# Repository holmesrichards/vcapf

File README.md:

# Voltage controlled all pass filter

***Note**: At this point the main PCB has been tested and found to be satisfactory, but the first run jacks PCB had errors. They have been corrected [twice] in the design and Gerber files but the [re]corrected board has not been tested. But what are the chances I'd get something so simple wrong ~~twice~~ three times? Shut up, it was a rhetorical question.*

This is an all pass filter (APF) intended to transform LFO wave shapes.

An all pass filter, as the name suggests, passes sine waves of any frequency with no change in amplitude. What does change is the phase angle, the relationship between the zero crossings (or peaks) of the input signal and those of the output. The phase shift depends on the frequency. A single pole APF produces a phase shift varying from 0° at low frequency to -90º at the corner frequency to -180° at high frequency. A two pole APF gives a phase shift from 0° at low frequency to -180º at the corner frequency to -360° at high frequency — the latter half of which is the same as +180° to 0°:

Putting a non sine periodic wave through an APF changes the wave's shape, since the different harmonics undergo different phase changes; the peak to peak amplitude can change as well, but usually not by a lot. Since the human ear isn't very sensitive to harmonic phases, this doesn't do much of anything interesting to audio waves. But it can produce interesting variants of low frequency CV waveshapes.

This module provides single pole and two pole APF outputs. It has input jacks for an LFO signal and a ±5 V corner frequency control voltage. There are attenuator pots for both inputs, and a knob to set the initial corner frequency.

Simulation results of applying 1- and 2-pole APF with various corner frequencies to triangle, ramp, and square waves are shown below:

A sin wave will not change shape, but its phase shift may be useful, if you want to vary two patch parameters with out of phase sin waves.

## Circuit description

The circuit is a simple voltage controlled two pole low pass filter (LPF), plus fixed mixing stages for producing APF outputs.

We start with a two pole LPF. This is a very standard design based on the LM13700 OTA datasheet. An exponential converter section transforms the linear control voltage into an exponential control current. Since this module is not intended for audio there is no need for accurate 1 V/oct response, and in fact it is less than 1 V/oct to provide a more useful corner frequency range with ±5 V CV. The filter stages themselves are typical aside from the large (100 nF) capacitors used to optimize the module for low frequency inputs. There is no feedback path to provide resonance, since resonance is not very useful here.

To get APF outputs we use an idea called pole mixing. If the output of a single pole LPF is doubled and subtracted from its input, the result is a single pole APF. To get a two pole APF one can take the input, subtact four times the single pole LPF output, and add four times the two pole LPF output. These mixings are done in op amp mixer stages with fixed resistor inputs. These are inverting stages, which for the single pole APF gives un-inverted (0° phase shift) output at low frequency. For the two pole APF we get inverted (180° phase shift) output at low frequency, so for consistency this signal goes through an additional inverting stage to obtain an un-inverted signal at low frequency at the output jack.

## LM13700

I designed the PCB to use the DIP version of the LM13700. This chip is out of production and getting harder to come by, though the SOIC version is available. I found these SOIC to DIP breakouts

* Chip-Quik PA0005 [https://www.digikey.com/en/products/detail/chip-quik-inc/PA0005/5014715](https://www.digikey.com/en/products/detail/chip-quik-inc/PA0005/5014715)
* Chip-Quik PA0005C [https://www.digikey.com/en/products/detail/chip-quik-inc/PA0005C/12352178](https://www.digikey.com/en/products/detail/chip-quik-inc/PA0005C/12352178)

one or the other of which probably could be used to assemble this PCB with a SOIC LM13700 — the second of those is narrower but costs more, and I think the first would work. (But I have a stash of DIP LM13700, so I haven't tried this.)

## Current draw
? mA +12 V, ? mA -12 V

## Photos

## Documentation

* [Schematic](Docs/vcapf.pdf)
* PCB layout: [front](Docs/vcapf_layout_front.pdf), [back](Docs/vcapf_layout_back.pdf)
* [BOM](Docs/vcapf_bom.md)
* [Build notes](Docs/build.md)
* [Blog post](https://analogoutputblog.wordpress.com/2022/05/07/voltage-controlled-all-pass-filter/)

## GitHub repository

* [https://github.com/holmesrichards/vcapf](https://github.com/holmesrichards/vcapf)

## Submodules

This repo uses submodules aoKicad and Kosmo_panel, which provide needed libaries for KiCad. To clone:

```
git clone git@github.com:holmesrichards/vcapf.git
git submodule init
git submodule update
```

Alternatively do

```
git clone --recurse-submodules git@github.com:holmesrichards/vcapf.git
```

Or if you download the repository as a zip file, you must also click on the "aoKicad" and "Kosmo\_panel" links on the GitHub page (they'll have "@ something" after them) and download them as separate zip files which you can unzip into this repo's aoKicad and Kosmo\_panel directories.

If desired, copy the files from aoKicad and Kosmo\_panel to wherever you prefer (your KiCad user library directory, for instance, if you have one). Then in KiCad, go into Edit Symbols and add symbol libraries 

```
aoKicad/ao_symbols
Kosmo_panel/Kosmo
```
and go into Edit Footprints and add footprint libraries 
```
aoKicad/ao_tht
Kosmo_panel/Kosmo_panel.
```

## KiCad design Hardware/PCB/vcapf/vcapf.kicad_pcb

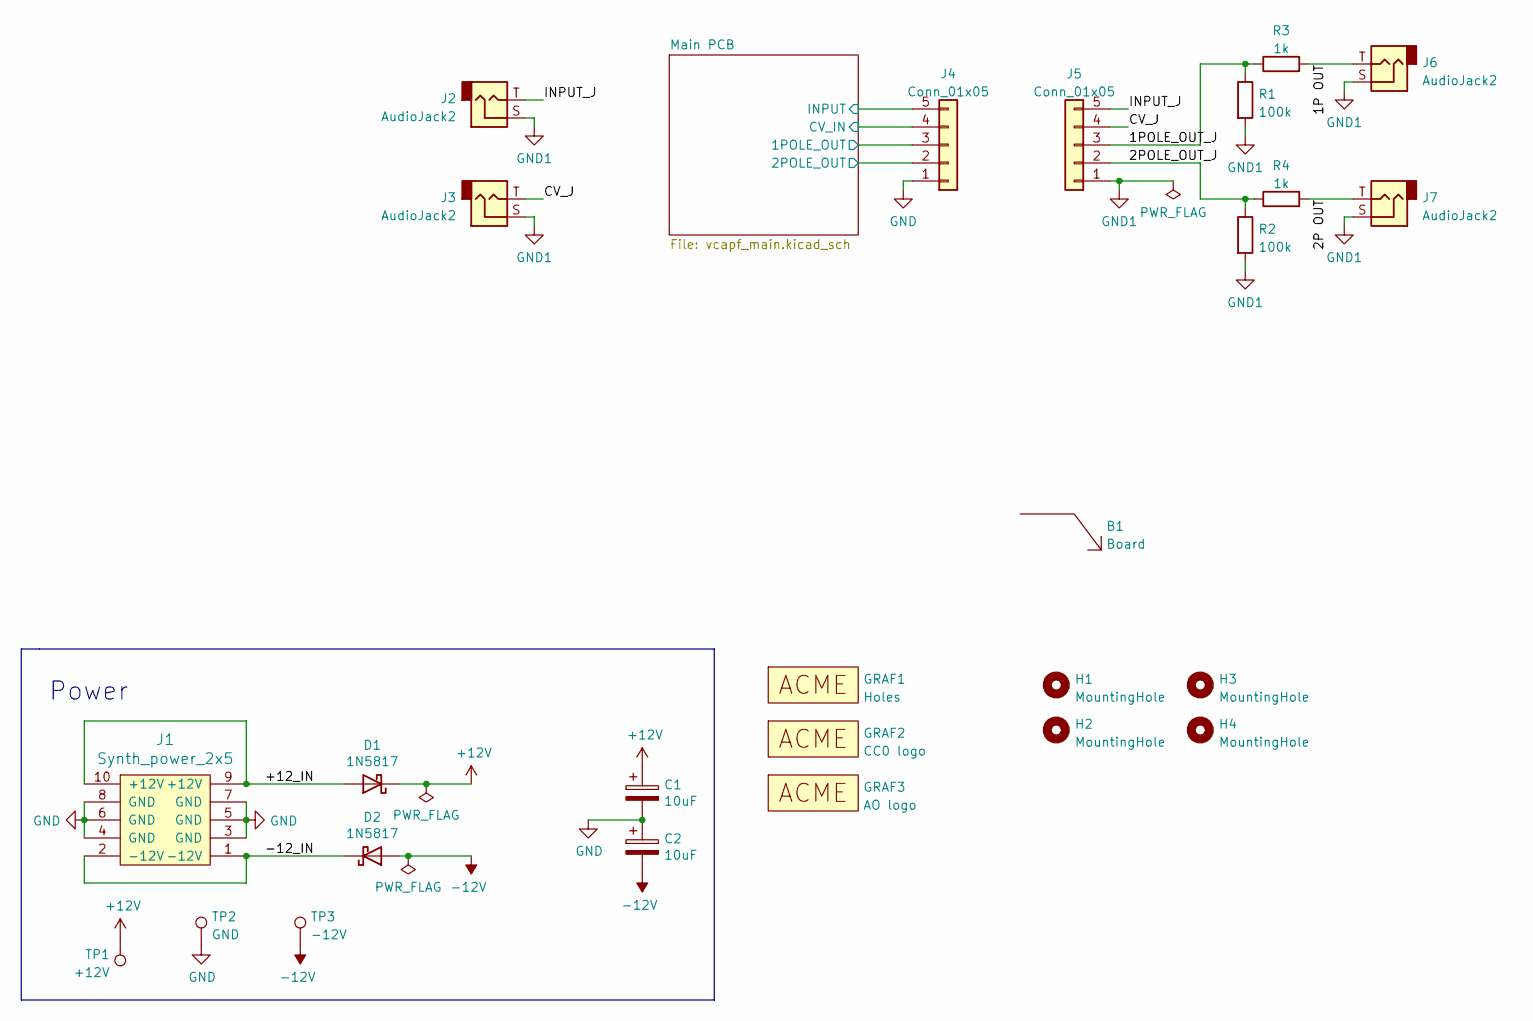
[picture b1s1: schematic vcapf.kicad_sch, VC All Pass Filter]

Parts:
B1: Board; Board_Marker
C1, C2: 10uF; CP_Radial_D6.3mm_P2.50mm
D1, D2: 1N5817; D_DO-41_SOD81_P10.16mm_Horizontal
GRAF1: Holes; vcapf_panel_holes
GRAF2: CC0 logo; CC0_logo
GRAF3: AO logo; analogoutput
H1, H2, H3, H4: MountingHole; MountingHole_3.2mm_M3
J1: Synth_power_2x5; Power_Header
J2, J3, J6, J7: AudioJack2; Jack_6.35mm_PJ_629HAN_slots
J4: Conn_01x05; PinSocket_1x05_P2.54mm_Vertical
J5: Conn_01x05; PinHeader_1x05_P2.54mm_Vertical
R1, R2: 100k; R_Axial_DIN0207_L6.3mm_D2.5mm_P10.16mm_Horizontal
R3, R4: 1k; R_Axial_DIN0207_L6.3mm_D2.5mm_P10.16mm_Horizontal
TP1: +12V; TestPoint_THTPad_D1.5mm_Drill0.7mm
TP2: GND; TestPoint_THTPad_1.5x1.5mm_Drill0.7mm
TP3: -12V; TestPoint_THTPad_D1.5mm_Drill0.7mm

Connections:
+12V: C1.1, D1.1 (K), TP1.1; also elsewhere on the board
-12V: C2.2, D2.2 (A), TP3.1; also elsewhere on the board
/1P OUT: J6.T, R3.2
/1POLE_OUT_J: J5.3, R1.1, R3.1
/2P OUT: J7.T, R4.2
/2POLE_OUT_J: J5.2, R2.1, R4.1
/+12_IN: D1.2 (A), J1.9 (+12V), J1.10 (+12V)
/-12_IN: D2.1 (K), J1.1 (-12V), J1.2 (-12V)
/CV_J: J3.T, J5.4
/INPUT_J: J2.T, J5.5
/Main PCB/1POLE_OUT: J4.3; also elsewhere on the board
/Main PCB/2POLE_OUT: J4.2; also elsewhere on the board
/Main PCB/CV_IN: J4.4; also elsewhere on the board
/Main PCB/INPUT: J4.5; also elsewhere on the board
GND: C1.2, C2.1, J1.3 (GND), J1.4 (GND), J1.5 (GND), J1.6 (GND), J1.7 (GND), J1.8 (GND), J4.1, TP2.1; also elsewhere on the board
GND1: J2.S, J3.S, J5.1, J6.S, J7.S, R1.2, R2.2

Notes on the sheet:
Power

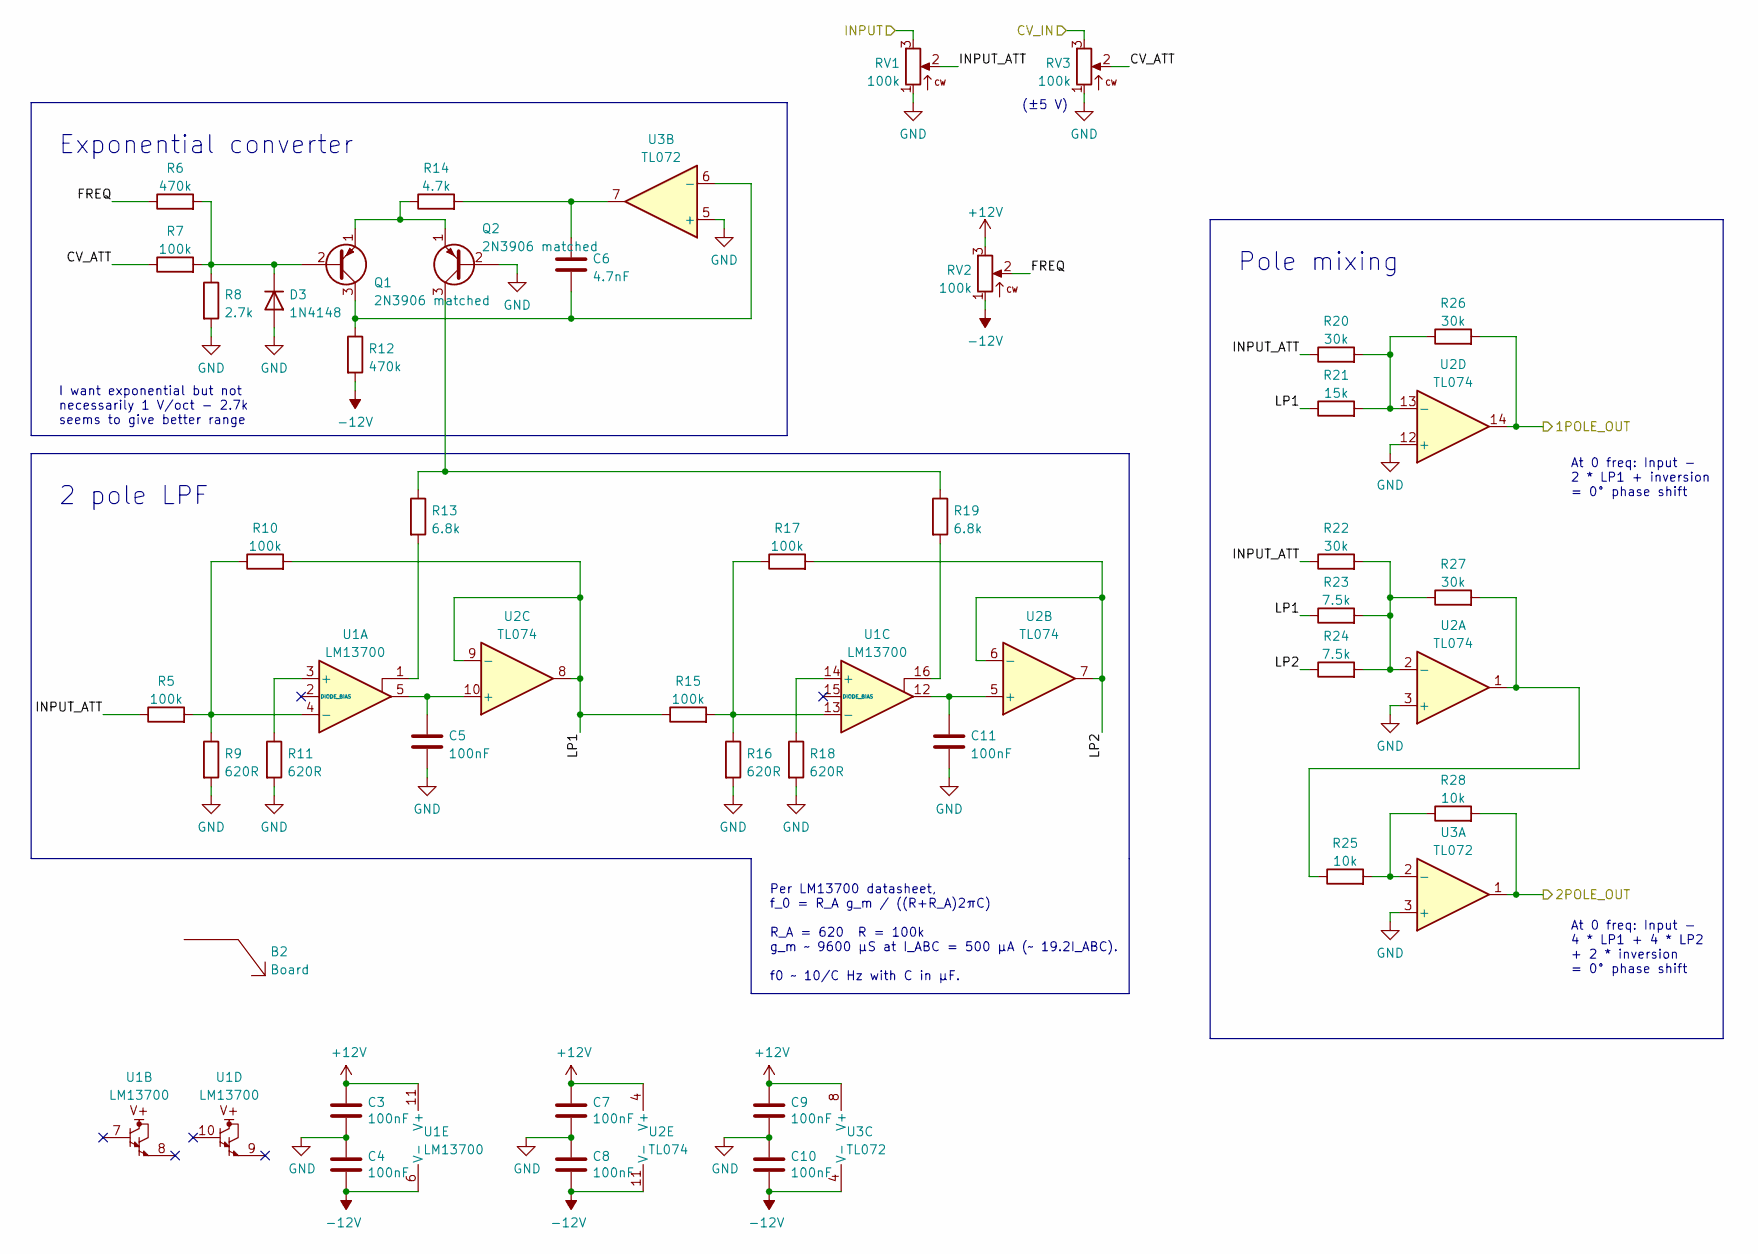
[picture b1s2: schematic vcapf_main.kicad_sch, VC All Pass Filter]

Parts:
B2: Board; Board_Marker
C3, C4, C7, C8, C9, C10: 100nF; C_Disc_D3.0mm_W1.6mm_P2.50mm
C5, C11: 100nF; C_Rect_L7.2mm_W2.5mm_P5.00mm_FKS2_FKP2_MKS2_MKP2
C6: 4.7nF; C_Disc_D5.0mm_W2.5mm_P5.00mm
D3: 1N4148; D_DO-35_SOD27_P7.62mm_Horizontal
Q1, Q2: 2N3906 matched; TO-92_Inline_Wide
R5, R7, R10, R15, R17: 100k; R_Axial_DIN0207_L6.3mm_D2.5mm_P10.16mm_Horizontal
R6, R12: 470k; R_Axial_DIN0207_L6.3mm_D2.5mm_P10.16mm_Horizontal
R8: 2.7k; R_Axial_DIN0207_L6.3mm_D2.5mm_P10.16mm_Horizontal
R9, R11, R16, R18: 620R; R_Axial_DIN0207_L6.3mm_D2.5mm_P10.16mm_Horizontal
R13, R19: 6.8k; R_Axial_DIN0207_L6.3mm_D2.5mm_P10.16mm_Horizontal
R14: 4.7k; R_Axial_DIN0207_L6.3mm_D2.5mm_P10.16mm_Horizontal
R20, R22, R26, R27: 30k; R_Axial_DIN0207_L6.3mm_D2.5mm_P10.16mm_Horizontal
R21: 15k; R_Axial_DIN0207_L6.3mm_D2.5mm_P10.16mm_Horizontal
R23, R24: 7.5k; R_Axial_DIN0207_L6.3mm_D2.5mm_P10.16mm_Horizontal
R25, R28: 10k; R_Axial_DIN0207_L6.3mm_D2.5mm_P10.16mm_Horizontal
RV1, RV2, RV3: 100k; Potentiometer_Alpha_16mm_Single_Vertical
U1: LM13700; DIP-16_W7.62mm_Socket_LongPads
U2: TL074; DIP-14_W7.62mm_Socket_LongPads
U3: TL072; DIP-8_W7.62mm_Socket_LongPads

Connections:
+12V: C3.1, C7.1, C9.1, RV2.3, U1.11 (V+), U2.4 (V+), U3.8 (V+); also elsewhere on the board
-12V: C4.2, C8.2, C10.2, R12.2, RV2.1, U1.6 (V-), U2.11 (V-), U3.4 (V-); also elsewhere on the board
/Main PCB/1POLE_OUT: R26.2, U2.14; also elsewhere on the board
/Main PCB/2POLE_OUT: R28.2, U3.1; also elsewhere on the board
/Main PCB/CV_ATT: R7.1, RV3.2
/Main PCB/CV_IN: RV3.3; also elsewhere on the board
/Main PCB/FREQ: R6.1, RV2.2
/Main PCB/INPUT: RV1.3; also elsewhere on the board
/Main PCB/INPUT_ATT: R5.1, R20.1, R22.1, RV1.2
/Main PCB/LP1: R10.2, R15.1, R21.1, R23.1, U2.8, U2.9 (-)
/Main PCB/LP2: R17.2, R24.1, U2.6 (-), U2.7
GND: C3.2, C4.1, C5.2, C7.2, C8.1, C9.2, C10.1, C11.2, D3.2 (A), Q2.2 (B), R8.2, R9.2, R11.2, R16.2, R18.2, RV1.1, RV3.1, U2.3 (+), U2.12 (+), U3.3 (+), U3.5 (+); also elsewhere on the board
unnamed: C5.1, U1.5, U2.10 (+)
unnamed: C6.1, R14.2, U3.7
unnamed: C6.2, Q1.3 (C), R12.1, U3.6 (-)
unnamed: C11.1, U1.12, U2.5 (+)
unnamed: D3.1 (K), Q1.2 (B), R6.2, R7.2, R8.1
unnamed: Q1.1 (E), Q2.1 (E), R14.1
unnamed: Q2.3 (C), R13.1, R19.1
unnamed: R5.2, R9.1, R10.1, U1.4 (-)
unnamed: R11.1, U1.3 (+)
unnamed: R13.2, U1.1
unnamed: R15.2, R16.1, R17.1, U1.13 (-)
unnamed: R18.1, U1.14 (+)
unnamed: R19.2, U1.16
unnamed: R20.2, R21.2, R26.1, U2.13 (-)
unnamed: R22.2, R23.2, R24.2, R27.1, U2.2 (-)
unnamed: R25.1, R27.2, U2.1
unnamed: R25.2, R28.1, U3.2 (-)

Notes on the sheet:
(±5 V)
Per LM13700 datasheet, f_0 = R_A g_m / ((R+R_A)2πC) R_A = 620 R = 100k g_m ~ 9600 µS at I_ABC = 500 µA (~ 19.2I_ABC). f0 ~ 10/C Hz with C in µF.
2 pole LPF
At 0 freq: Input - 4 * LP1 + 4 * LP2 + 2 * inversion = 0° phase shift
At 0 freq: Input - 2 * LP1 + inversion = 0° phase shift
I want exponential but not necessarily 1 V/oct - 2.7k seems to give better range
Exponential converter
Pole mixing

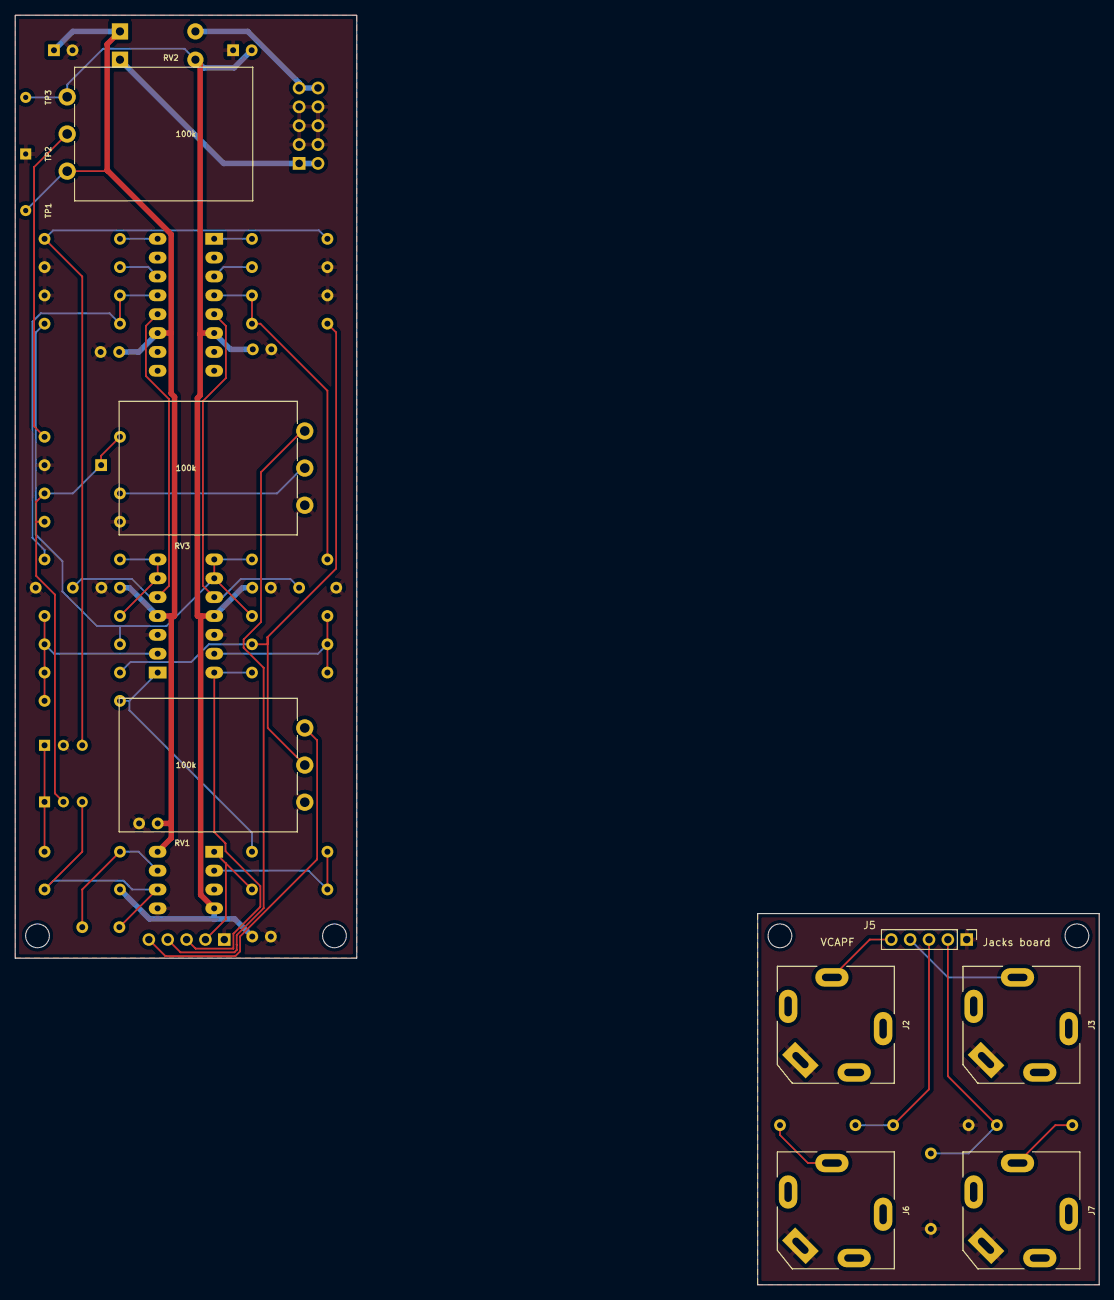
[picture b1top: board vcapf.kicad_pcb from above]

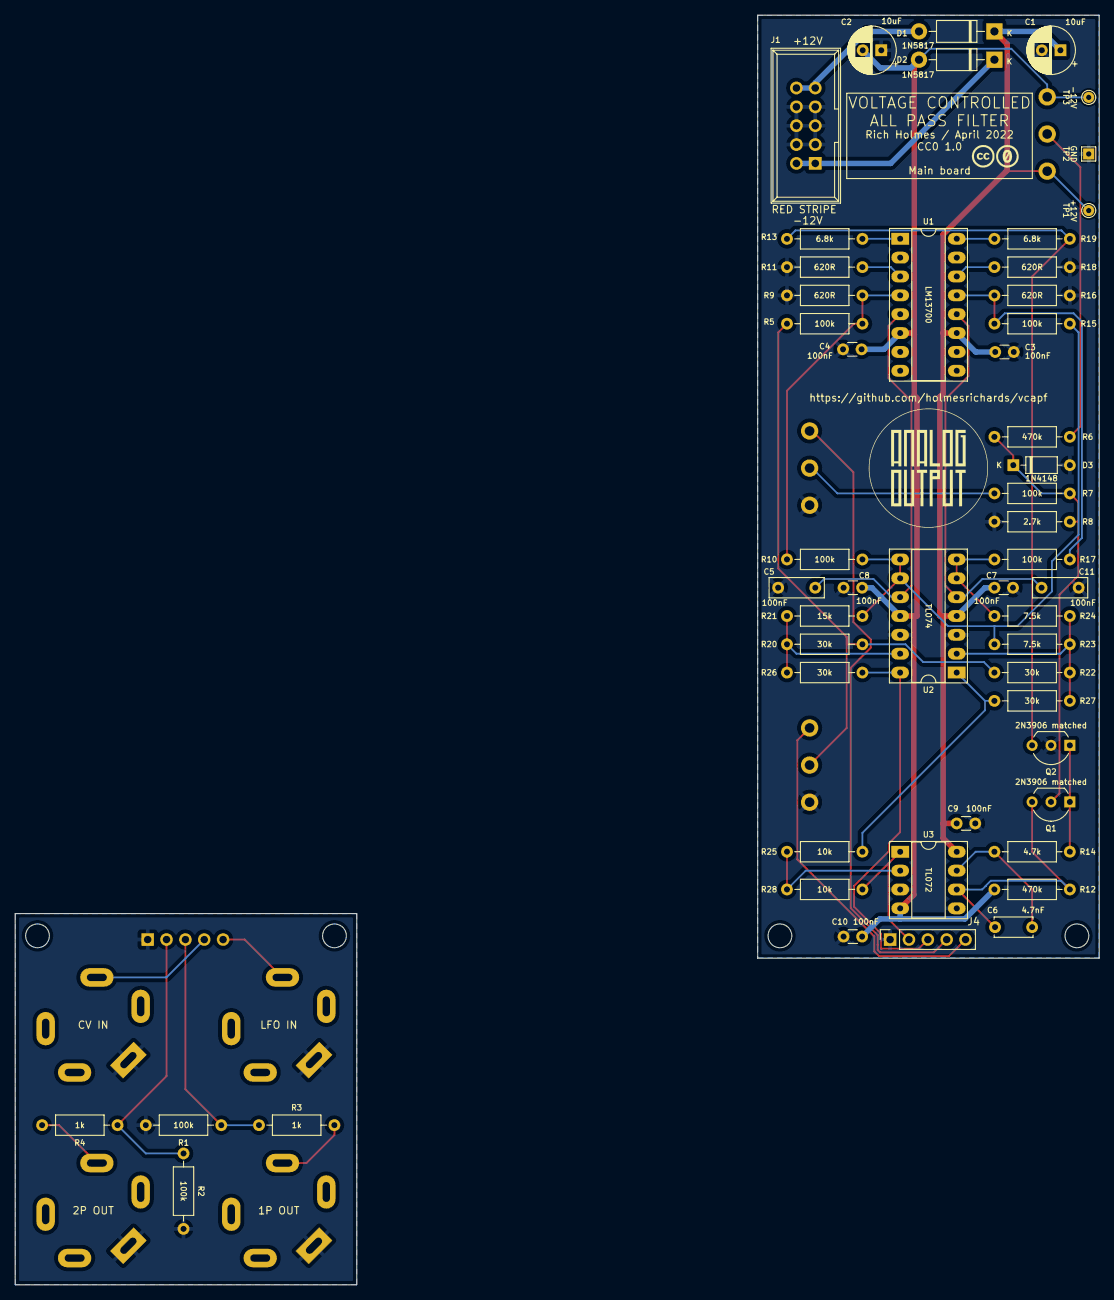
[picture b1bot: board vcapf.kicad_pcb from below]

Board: 2 copper layers, 146.0 x 171.0 mm, 69 parts (54 on the bottom side), 38 nets.

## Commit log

2022-04-04 Initial version
2022-04-06 Schem PDF
2022-04-07 Post breadboard tweaks; layout
2022-04-08 Layout corrections, pot position and main board length
2022-04-09 Net labels, panel
2022-04-10 Libraries, readme, rm old sims and notes
2022-04-10 Match transistors
2022-04-17 BOM, README revision
2022-05-07 Pre fab tweaks, unreverse jacks, Gerbers
2022-05-07 Post fab updates
2022-05-07 LICENSE
2022-05-07 link
2022-05-07 Blog post
2022-05-07 Rename file to remove blanks
2022-05-07 rm blanky name file
2022-05-07 Fix blanky file name
2022-05-18 Fill jacks board
